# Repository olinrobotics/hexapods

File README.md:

# hexapods
Space! Rovers! Too many legs...

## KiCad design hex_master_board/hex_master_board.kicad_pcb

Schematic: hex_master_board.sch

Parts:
C1, C4: 1uF; C_0805_2012Metric_Pad1.15x1.40mm_HandSolder
C2, C3, C5, C6, C11, C12, C13: 0.1uF; C_0805_2012Metric_Pad1.15x1.40mm_HandSolder
C7, C9: 18pF; C_0805_2012Metric_Pad1.15x1.40mm_HandSolder
C8, C10, C14, C15, C16: 10uF; C_0805_2012Metric_Pad1.15x1.40mm_HandSolder
D1, D2: LED; LED_SMD_1206
D3: POWER; LED_SMD_1206
D4: IO_LED; LED_SMD_1206
J1: USB_B_Micro; USB micro 609-4616-1-ND
R1, R6, R13: 1kΩ; R_0805_2012Metric_Pad1.15x1.40mm_HandSolder
R2, R3, R4, R5, R8, R12, R15: 1k; R_0805_2012Metric_Pad1.15x1.40mm_HandSolder
R7, R14, R16, R17, R18, R19, R20, R21, R22, R23, R24, R25, R26, R27, R28: 10k; R_0805_2012Metric_Pad1.15x1.40mm_HandSolder
R9: 20K; R_0805_2012Metric_Pad1.15x1.40mm_HandSolder
R10: 10K; R_0805_2012Metric_Pad1.15x1.40mm_HandSolder
R11: 1K; R_0805_2012Metric_Pad1.15x1.40mm_HandSolder
S0, S1, S2, S3, S4, S5, S6, S7, S8, S9, S10, S11: SW_DIP_x01; switch_ins
U1, U12: Jack_CP-002B-ND
U2: 74LVC1G157GV_MUX2; 74LVC1G157_MUX2_TSOP6
U3: AP2210N-5.0TRG1-lin-reg; SOT-23
U4: FT232RL; SSOP-28_5.3x10.2mm_P0.65mm
U5: TPS2113A; TPS2113ADRBR
U6: Pushbutton_Stockroom
U7: ATmega2561-16AU; TQFP-64_14x14mm_P0.8mm
U8, U9: PCA9685PW; TSSOP-28_4.4x9.7mm_P0.65mm
U10, U11, U29, U30: EXB-2HV221JV
U13, U14, U15, U16, U17, U18, U19, U20, U21, U22, U23, U24, U25, U26, U27, U28, U31, U32, U33, U34, U35, U36, U37, U38, U39, U40, U41, U42, U43, U44, U45, U46: Servo_connector; servo_header
U47: ICSP_breakout; ICSP_header_0.1
U48: header_0.1_8_powered; header_0.1_8_power
U49, U50: header_0.1_8; header_0.1_8x
U51: LIS3DH_breakout; LIS3DH_IMU_BOARD
U52: header_0.1_I2C; header_0.1_i2c_12
U53: header_0.1_xbee
Y1: Crystal; Crystal_osc_535-10226-1-ND

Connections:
/A0: U7.61 (PF0), U48.1
/A1: U7.60 (PF1), U48.2
/A2: U7.59 (PF2), U48.3
/A3: U7.58 (PF3), U48.4
/A4: U7.57 (PF4), U48.5
/A5: U7.56 (PF5), U48.6
/A6: U7.55 (PF6), U48.7
/A7: U7.54 (PF7), U48.8
/Atmega_RXD0: R8.1, U7.2 (PE0)
/Atmega_TXD0: R2.1, R3.1, U7.3 (PE1)
/D0: D4.2, R17.2, S0.1, U7.51 (PA0)
/D1: R18.2, S1.1, U7.50 (PA1)
/D2: R19.2, S2.1, U7.49 (PA2)
/D3: R20.2, S3.1, U7.48 (PA3)
/D4: R21.2, S4.1, U7.47 (PA4)
/D5: R22.2, S5.1, U7.46 (PA5)
/D6: R23.2, S6.1, U7.45 (PA6)
/D7: R24.2, S7.1, U7.44 (PA7)
/D8: R25.2, S8.1, U7.10 (PB0)
/D9: R26.2, S9.1, U7.14 (PB4)
/D10: R27.2, S10.1, U7.15 (PB5)
/D11: R28.2, S11.1, U7.16 (PB6)
/D13: U7.4 (PE2), U50.1
/D14: U7.5 (PE3), U50.2
/D15: U7.6 (PE4), U50.3
/D16: U7.7 (PE5), U50.4
/D17: U7.8 (PE6), U50.5
/D18: U7.9 (PE7), U50.6
/D19: U7.35 (PC0), U50.7
/D20: U7.36 (PC1), U50.8
/D21: U7.37 (PC2), U49.1
/D22: U7.38 (PC3), U49.2
/D23: U7.39 (PC4), U49.3
/D24: U7.40 (PC5), U49.4
/D25: U7.41 (PC6), U49.5
/D26: U7.42 (PC7), U49.6
/MISO: U7.13 (PB3), U47.1
/MOSI: U7.12 (PB2), U47.5
/SCK: U7.11 (PB1), U47.2
/SCL: R14.2, U7.25 (PD0), U8.26, U9.26, U51.4, U52.4
/SDA: R16.2, U7.26 (PD1), U8.27, U9.27, U51.5, U52.3
/SSIG_0: U10.16, U13.2
/SSIG_1: U10.15, U14.2
/SSIG_2: U10.14, U15.2
/SSIG_3: U10.13, U16.2
/SSIG_4: U10.12, U17.2
/SSIG_5: U10.11, U18.2
/SSIG_6: U10.10, U19.2
/SSIG_7: U10.9, U20.2
/SSIG_8: U11.16, U21.2
/SSIG_9: U11.15, U22.2
/SSIG_10: U11.14, U23.2
/SSIG_11: U11.13, U24.2
/SSIG_12: U11.12, U25.2
/SSIG_13: U11.11, U26.2
/SSIG_14: U11.10, U27.2
/SSIG_15: U11.9, U28.2
/SSIG_16: U29.16, U31.2
/SSIG_17: U29.15, U32.2
/SSIG_18: U29.14, U33.2
/SSIG_19: U29.13, U34.2
/SSIG_20: U29.12, U35.2
/SSIG_21: U29.11, U36.2
/SSIG_22: U29.10, U37.2
/SSIG_23: U29.9, U38.2
/SSIG_24: U30.16, U39.2
/SSIG_25: U30.15, U40.2
/SSIG_26: U30.14, U41.2
/SSIG_27: U30.13, U42.2
/SSIG_28: U30.12, U43.2
/SSIG_29: U30.11, U44.2
/SSIG_30: U30.10, U45.2
/SSIG_31: U30.9, U46.2
/USB_RXD: R3.2, U4.5
/USB_TXD: R4.1, U4.1
/USB_V+: C8.1, J1.1, R7.1, U2.6, U5.6
/XBEE_RXD: R2.2, U53.3
/XBEE_TXD: R5.2, U53.4
/servo_power: C16.1, U12.1, U13.1, U14.1, U15.1, U16.1, U17.1, U18.1, U19.1, U20.1, U21.1, U22.1, U23.1, U24.1, U25.1, U26.1, U27.1, U28.1, U31.1, U32.1, U33.1, U34.1, U35.1, U36.1, U37.1, U38.1, U39.1, U40.1, U41.1, U42.1, U43.1, U44.1, U45.1, U46.1
/~RESET: C6.1, R12.2, U6.2, U7.20 (~RESET), U47.3
/~RX_LED: R6.2, U4.23
/~TX_LED: R1.2, U4.22
GND: C1.2, C2.2, C3.2, C4.2, C5.2, C7.2, C8.2, C9.2, C10.2, C11.2, C12.2, C13.2, C14.2, C15.2, C16.2, J1.5, R7.2, R10.2, R11.2, R13.2, R15.2, S0.2, S1.2, S2.2, S3.2, S4.2, S5.2, S6.2, S7.2, S8.2, S9.2, S10.2, S11.2, U1.2, U2.2, U3.1, U4.7, U4.18, U4.21, U4.25, U4.26, U5.2, U5.5, U6.4, U7.22 (GND), U7.53 (GND), U7.63 (GND), U8.1, U8.2, U8.3, U8.4, U8.5, U8.14, U8.23, U8.24, U8.25, U9.2, U9.3, U9.4, U9.5, U9.14, U9.23, U9.24, U9.25, U12.2, U13.3, U14.3, U15.3, U16.3, U17.3, U18.3, U19.3, U20.3, U21.3, U22.3, U23.3, U24.3, U25.3, U26.3, U27.3, U28.3, U31.3, U32.3, U33.3, U34.3, U35.3, U36.3, U37.3, U38.3, U39.3, U40.3, U41.3, U42.3, U43.3, U44.3, U45.3, U46.3, U47.4, U48.10, U51.3, U52.2, U53.1
unnamed: C1.1, U1.1, U3.3
unnamed: C4.1, R9.1, U3.2, U5.8
unnamed: C6.2, U4.2
unnamed: C7.1, U7.24 (XTAL1), Y1.1
unnamed: C9.1, U7.23 (XTAL2), Y1.2
unnamed: C11.1, U7.62 (AREF)
unnamed: D1.1, R1.1
unnamed: D2.1, R6.1
unnamed: D3.1, R13.1
unnamed: D4.1, R15.1
unnamed: J1.2, U4.16
unnamed: J1.3, U4.15
unnamed: R4.2, U2.3
unnamed: R5.1, U2.1
unnamed: R8.2, U2.4
unnamed: R9.2, R10.1, U5.3
unnamed: R11.1, U5.4
unnamed: U8.6, U10.1
unnamed: U8.7, U10.2
unnamed: U8.8, U10.3
unnamed: U8.9, U10.4
unnamed: U8.10, U10.5
unnamed: U8.11, U10.6
unnamed: U8.12, U10.7
unnamed: U8.13, U10.8
unnamed: U8.15, U11.1
unnamed: U8.16, U11.2
unnamed: U8.17, U11.3
unnamed: U8.18, U11.4
unnamed: U8.19, U11.5
unnamed: U8.20, U11.6
unnamed: U8.21, U11.7
unnamed: U8.22, U11.8
unnamed: U9.6, U29.1
unnamed: U9.7, U29.2
unnamed: U9.8, U29.3
unnamed: U9.9, U29.4
unnamed: U9.10, U29.5
unnamed: U9.11, U29.6
unnamed: U9.12, U29.7
unnamed: U9.13, U29.8
unnamed: U9.15, U30.1
unnamed: U9.16, U30.2
unnamed: U9.17, U30.3
unnamed: U9.18, U30.4
unnamed: U9.19, U30.5
unnamed: U9.20, U30.6
unnamed: U9.21, U30.7
unnamed: U9.22, U30.8

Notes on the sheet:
Power Multiplexing
USB/UART
Atmega
PWM Drivers
Don't forget to add resistors to outputs
LED
Switch Inputs
These are for switches on the hexapod feet Internal pull-ups, D0-D5
Serial Multiplexing
Make sure using power as a logic level isn't sketchy
Reset Button
Logic Power
Servo Ports
Comm LEDs
FT232RQ
IO Breakouts
ICSP Headers
Hexapod Control Board V0 --- DRAFT
Accelerometer
Communicates with Atmega over I2C

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
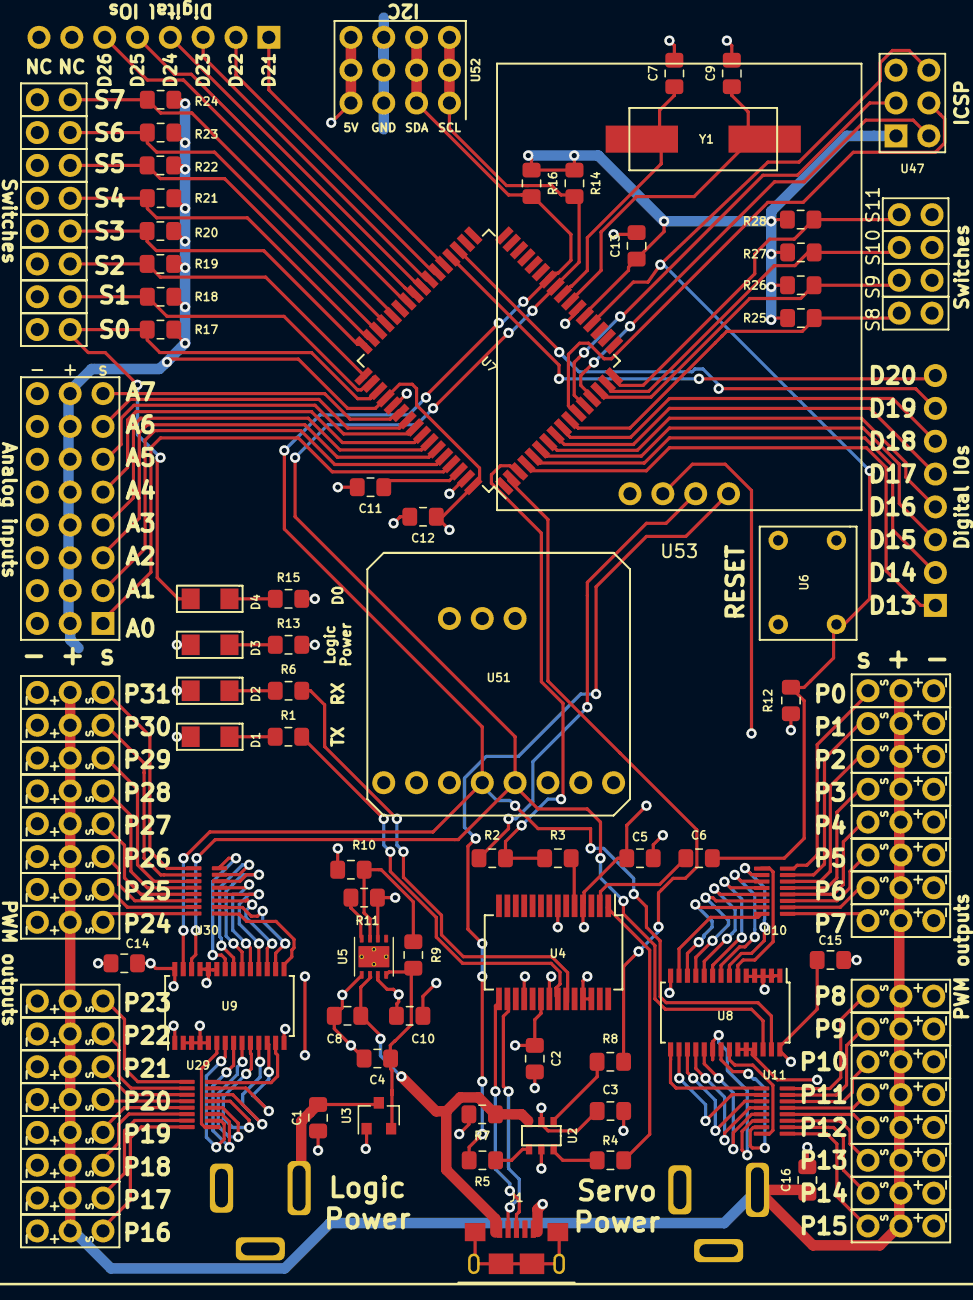
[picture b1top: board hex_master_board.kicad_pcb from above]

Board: 2 copper layers, 115 parts (0 on the bottom side), 133 nets.

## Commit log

2018-09-19 Control all three servos simultaneously. Not great e-stop.
2018-09-21 Software e-stop implemented
2018-09-21 Removed bug that caused movement when entering testing state
2018-09-26 Restructured code to use arrays
2018-09-28 Added preprogrammed positions for quick testing
2018-09-28 Add ros architecture, custom services and messages
2018-10-05 built framework for genetic algorithm, the (pseduo)random generation of new step sets, translation of step sets to file
2018-10-05 Move matlab script into github
2018-10-05 Add 3D model for forward kinematics
2018-10-05 Move leg
2018-10-10 initial generation of genetics is working off-robot
2018-10-13 example code from adafruit for driving servos from servo shield
2018-10-17 add code to control relay in servo example code
2018-10-17 Inverse kinematics Arduino code
2018-10-17 Inverse kinematics arduino code tested on the hexapod
2018-10-17 Moved inverse kinematics Matlab and Mathematica scripts into repository
2018-10-19 Untested walking code
2018-10-20 Walking code tested with 2 legs on hexapod
2018-10-26 building gazebo model of hexapod
2018-10-26 Accelerometer test code
2018-10-31 Power diagram picture
2018-11-02 put old kinematics into a folder
2018-11-02 finishing moving files into inverse_kinematics_testing
2018-11-02 Moved relevant files to kinematics folder
2018-11-02 more organization
2018-11-02 Updated walking code for 2 servo shields
2018-11-03 Fixed Arduino version compatibility issues
2018-11-03 Hexapod walking code fully tested
2018-11-03 Updated servo testing code
2018-11-07 Added turning functionality and experimented with custom libraries
2018-11-07 fleshing out more of genetic algorithm
2018-11-09 testing and style
2018-11-10 Added hexapod sitting code
2018-11-16 Standing code
2018-11-28 Moved low-level hexapod code into separate file
2018-11-28 Moved step timing code into Hexapod class
2018-12-01 Fall prevention code
2018-12-05 Python lidar code
2018-12-05 adding IR sensor library
2018-12-05 Added IR sensor to flight code
2018-12-05 Added waypoints
2018-12-05 Right IR sensor in flight code
2018-12-07 fleshing out genetics
2018-12-07 fixed SharpIR ID#
2018-12-07 some trial IR code
2018-12-12 not actually sure?
2018-12-12 fixed the walk-in-place problem. Now will stop when it detects a wall.
2018-12-14 XBee testing
2018-12-14 Integrated IR with foot sensor
2018-12-15 framework for trynewpath
2018-12-15 Added additional waypoint types
2018-12-15 Tested new waypoint types
2018-12-15 addition of wander state
2018-12-16 wander state slightly better
2018-12-17 not sure. Maybe spaces or something?
2019-02-10 Rough terrain walking code
2019-03-02 Auto-leveling between steps
2019-03-03 Created and tested Arduino serial communication and temporary python code to interface with it.
2019-03-03 Interpolating position instead of servo angle
2019-03-06 Renamed serial listener script, interfacing with ROS
2019-03-06 More useful class docstring, remove try/catch
2019-03-06 Add file description
2019-03-10 Added Arduino serial writing to stream sensor data
2019-03-10 Teleop body rotation
2019-04-17 Improved keyboard control
2019-04-17 Successfully reading values from the LIDAR
2019-04-26 Added LIDAR tilting code and changed hexapod gait
2019-04-26 Initial commit for PCB
2019-09-13 Commit local changes from last semester
2019-09-13 Add placeholder switch symbols and TODO list in schematic
2019-09-20 Changes as of semester end
2019-09-22 Change voltage regulator to one stocked by digikey
2019-09-24 Added servo outs to schematic
2019-09-27 Add additional switch inputs
2019-10-01 Add footprints to resistors, capacitors, switch inputs
2019-10-04 Add IO header symbol
2019-10-11 Updated gait for easier adaptation to cliff climbing
2019-10-11 Add footprint for ICSP header, associate footprint for switch inputs
2019-10-11 Fixed turning issues
2019-10-13 Leveling code tested successfully
2019-10-15 Start PCB layout!
2019-10-22 Footprint for crystal, develop footprint further
2019-10-25 More progress on layout
2019-11-01 Slope compensation implemented
2019-11-01 Parameter tuning for climbing
2019-11-03 Add accelerometer, more tracing
2019-11-03 Downhill walking tested
2019-11-15 Cleaned up old gait code
2019-12-06 Add I2C headers, fully connect board
2019-12-08 Integrate XBEE... Functionality on first-pass PCB is done!
2019-12-13 Teleop interface
2019-12-15 Add silk screen labels and olin logo
2019-12-15 Fixed walking without foot sensors
